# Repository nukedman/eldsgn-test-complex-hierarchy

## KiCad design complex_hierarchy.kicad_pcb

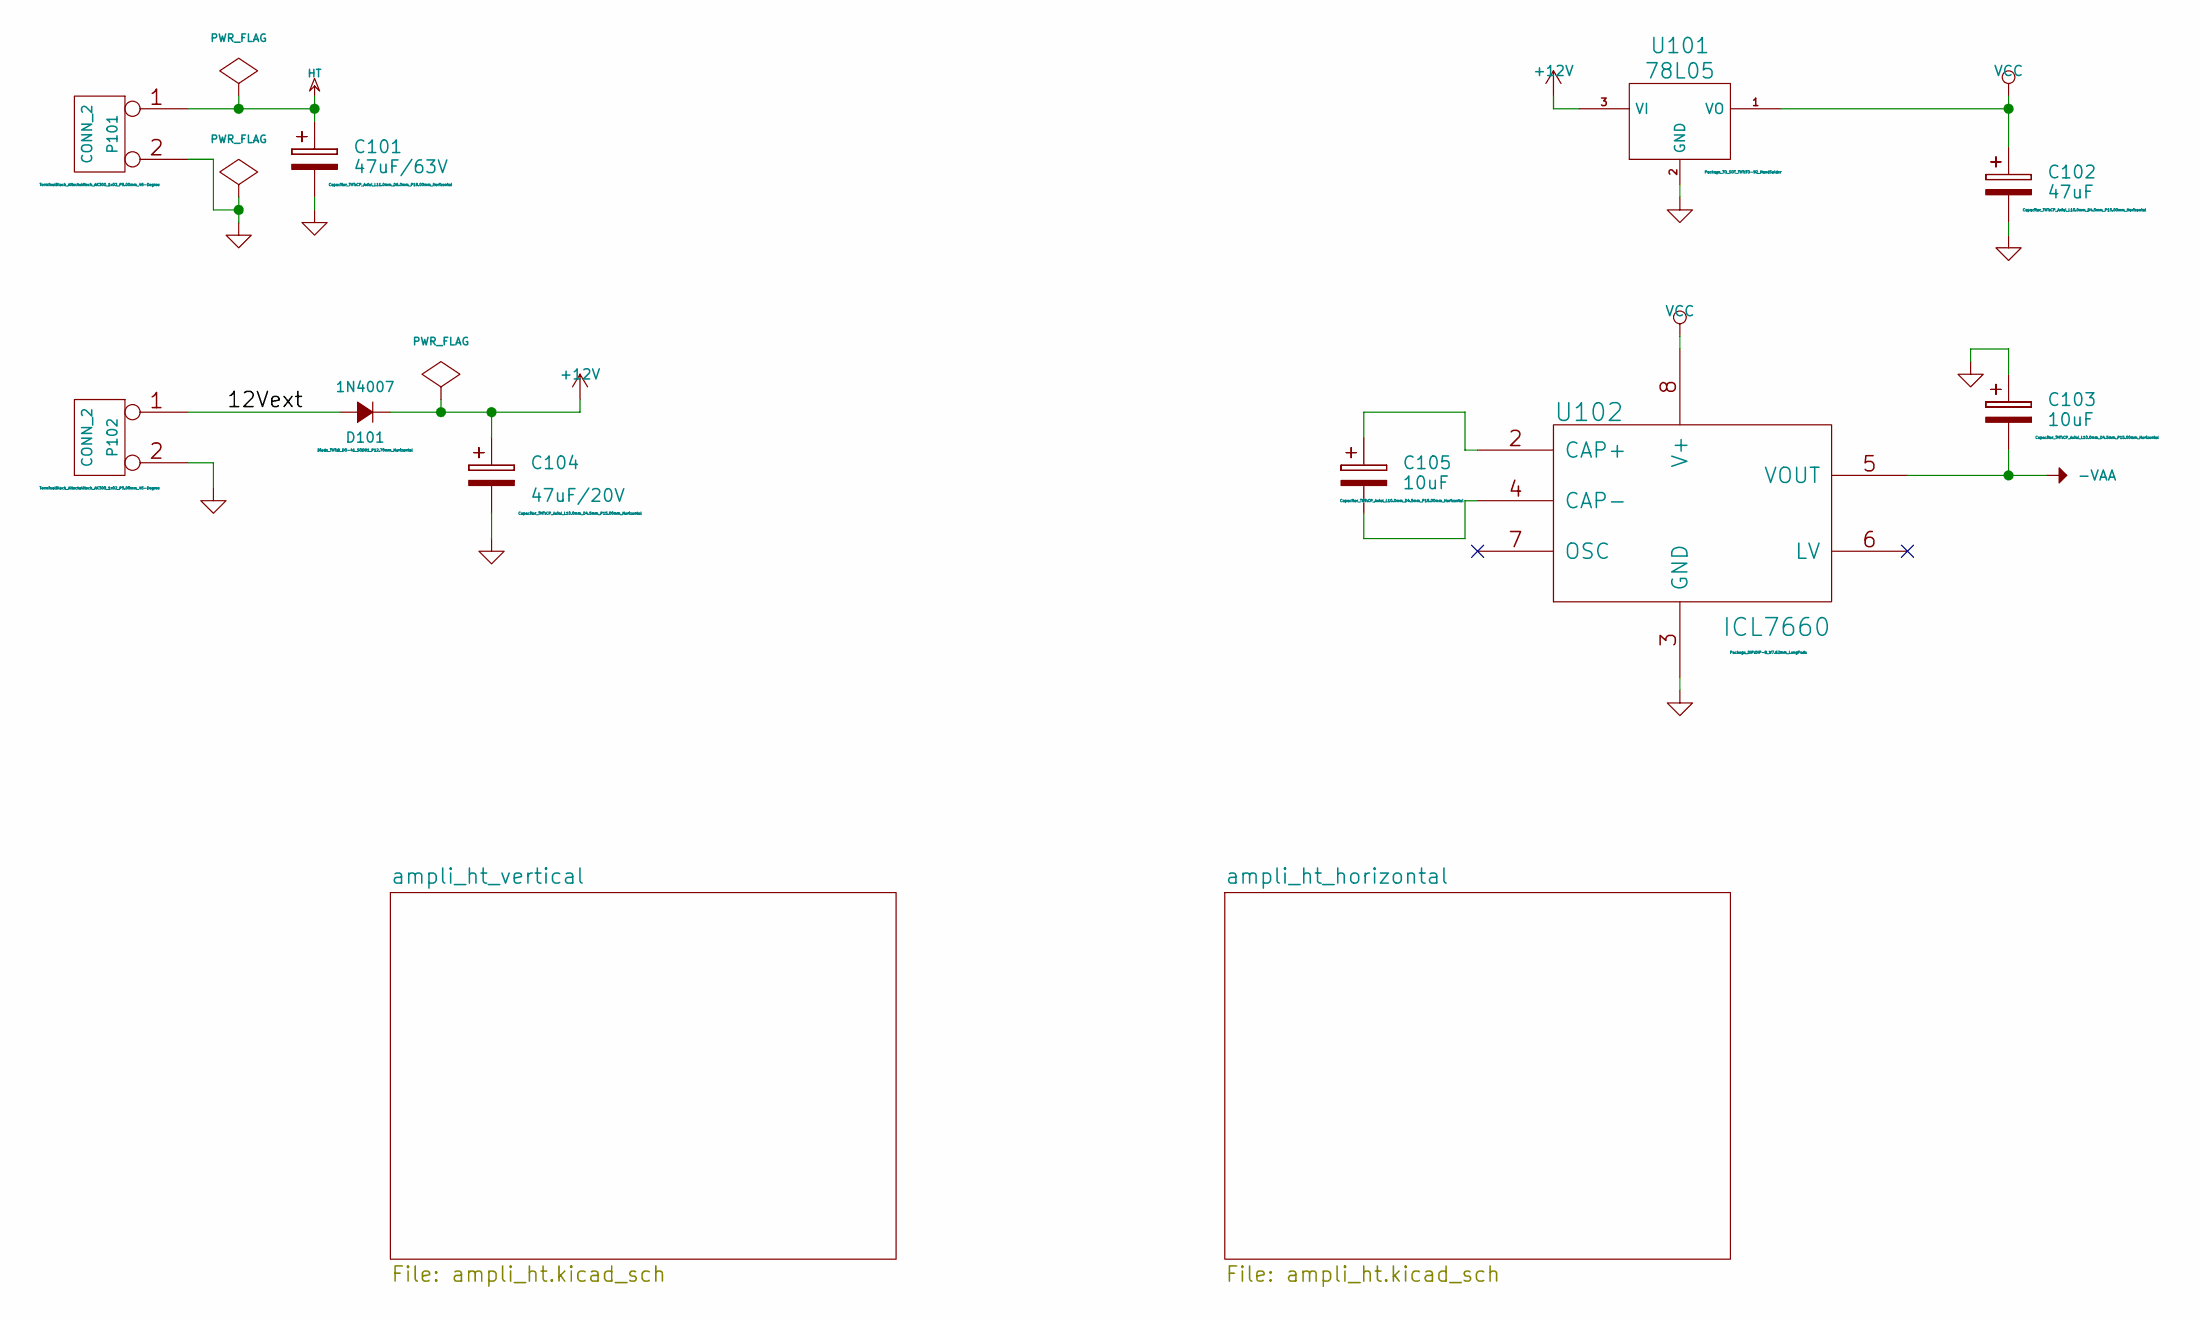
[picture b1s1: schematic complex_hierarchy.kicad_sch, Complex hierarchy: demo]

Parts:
C101: 47uF/63V; CP_Axial_L11.0mm_D6.0mm_P18.00mm_Horizontal
C102: 47uF; CP_Axial_L10.0mm_D4.5mm_P15.00mm_Horizontal
C103, C105: 10uF; CP_Axial_L10.0mm_D4.5mm_P15.00mm_Horizontal
C104: 47uF/20V; CP_Axial_L10.0mm_D4.5mm_P15.00mm_Horizontal
D101: 1N4007; D_DO-41_SOD81_P12.70mm_Horizontal
P101, P102: CONN_2; Altech_AK300_1x02_P5.00mm_45-Degree
U101: 78L05; TO-92_HandSolder
U102: ICL7660; DIP-8_W7.62mm_LongPads

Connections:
-VAA: C103.2, U102.5 (VOUT); also elsewhere on the board
/12Vext: D101.2 (A), P102.1
unnamed: C105.1, U102.2 (CAP+)
unnamed: C105.2, U102.4 (CAP-)
VCC: C102.1, U101.1 (VO), U102.8 (V+)

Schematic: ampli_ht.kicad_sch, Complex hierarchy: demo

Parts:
C201: 15nF; C_Disc_D5.0mm_W2.5mm_P5.00mm
C202: 150nF; C_Disc_D5.0mm_W2.5mm_P5.00mm
C203: 4.7nF; C_Disc_D5.0mm_W2.5mm_P5.00mm
C204: 820pF; C_Disc_D5.0mm_W2.5mm_P5.00mm
D201, D202, D203, D204: 1N4148; D_DO-35_SOD27_P7.62mm_Horizontal
P201, P202: CONN_2; Altech_AK300_1x02_P5.00mm_45-Degree
Q201, Q203: MPSA92; TO-92_HandSolder
Q202, Q204: MPSA42; TO-92_HandSolder
R1, R5: 0603WAF6201T5E; C4260; MPN 0603WAF6201T5E; LCSC Part C4260
R3: RC0402FR-07910RL2; C276279; MPN RC0402FR-07910RL; LCSC Part C276279
R201, R208, R212: 1K; R_Axial_DIN0204_L3.6mm_D1.6mm_P7.62mm_Horizontal
R202, R203: 22K; R_Axial_DIN0204_L3.6mm_D1.6mm_P7.62mm_Horizontal
R204: 470; R_Axial_DIN0204_L3.6mm_D1.6mm_P7.62mm_Horizontal
R205, R209, R210: 220K; R_Axial_DIN0204_L3.6mm_D1.6mm_P7.62mm_Horizontal
R206, R207: 47; R_Axial_DIN0204_L3.6mm_D1.6mm_P7.62mm_Horizontal
R211: 5,6K; R_Axial_DIN0204_L3.6mm_D1.6mm_P7.62mm_Horizontal
R213: 4,7K; R_Axial_DIN0204_L3.6mm_D1.6mm_P7.62mm_Horizontal
RV201: 4,7K; Potentiometer_Bourns_3266W_Vertical
U201: LM358N; DIP-8_W7.62mm_LongPads

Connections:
-VAA: U201.4 (V-); also elsewhere on the board
/ampli_ht_vertical/PIEZO_IN: P201.1, R1.1, R201.2
/ampli_ht_vertical/PIEZO_OUT: P202.1, R206.1, R207.1
/ampli_ht_vertical/S_OUT+: R209.1, R210.1, RV201.3
/ampli_ht_vertical/Vpil_0_3,3V: C201.1, R3.2, U201.3 (+), U201.6 (-), U201.7
unnamed: C201.2, R202.1, R203.2
unnamed: C202.1, R201.1, R202.2
unnamed: C204.1, R211.2
unnamed: D201.1 (K), D202.2 (A)
unnamed: D202.1 (K), Q201.2 (B), R205.1
unnamed: D203.2 (A), Q201.3 (C), Q202.2 (B)
unnamed: D203.1 (K), D204.2 (A)
unnamed: D204.1 (K), Q203.2 (B), Q204.3 (C), R211.1
unnamed: Q201.1 (E), R204.2
unnamed: Q202.1 (E), R206.2, R210.2
unnamed: Q203.1 (E), R207.2, R209.2
unnamed: Q204.2 (B), R208.1
unnamed: Q204.1 (E), R212.1
unnamed: R1.2, R3.1, R5.1 (1_1)
unnamed: R212.2, U201.1
unnamed: R213.1, RV201.1
unnamed: RV201.2, U201.2 (-)
unnamed: C203.1, R203.1, U201.5 (+)

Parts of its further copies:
C301: 15nF; C_Disc_D5.0mm_W2.5mm_P5.00mm
C302: 150nF; C_Disc_D5.0mm_W2.5mm_P5.00mm
C303: 4.7nF; C_Disc_D5.0mm_W2.5mm_P5.00mm
C304: 820pF; C_Disc_D5.0mm_W2.5mm_P5.00mm
D301, D302, D303, D304: 1N4148; D_DO-35_SOD27_P7.62mm_Horizontal
P301, P302: CONN_2; Altech_AK300_1x02_P5.00mm_45-Degree
Q301, Q303: MPSA92; TO-92_HandSolder
Q302, Q304: MPSA42; TO-92_HandSolder
R2, R6: 0603WAF6201T5E; C4260; MPN 0603WAF6201T5E; LCSC Part C4260
R4: RC0402FR-07910RL2; C276279; MPN RC0402FR-07910RL; LCSC Part C276279
R301, R308, R312: 1K; R_Axial_DIN0204_L3.6mm_D1.6mm_P7.62mm_Horizontal
R302, R303: 22K; R_Axial_DIN0204_L3.6mm_D1.6mm_P7.62mm_Horizontal
R304: 470; R_Axial_DIN0204_L3.6mm_D1.6mm_P7.62mm_Horizontal
R305, R309, R310: 220K; R_Axial_DIN0204_L3.6mm_D1.6mm_P7.62mm_Horizontal
R306, R307: 47; R_Axial_DIN0204_L3.6mm_D1.6mm_P7.62mm_Horizontal
R311: 5,6K; R_Axial_DIN0204_L3.6mm_D1.6mm_P7.62mm_Horizontal
R313: 4,7K; R_Axial_DIN0204_L3.6mm_D1.6mm_P7.62mm_Horizontal
RV301: 4,7K; Potentiometer_Bourns_3266W_Vertical
U301: LM358N; DIP-8_W7.62mm_LongPads

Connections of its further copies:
-VAA: U301.4 (V-); also elsewhere on the board
/ampli_ht_horizontal/PIEZO_IN: P301.1, R2.1, R301.2
/ampli_ht_horizontal/PIEZO_OUT: P302.1, R306.1, R307.1
/ampli_ht_horizontal/S_OUT+: R309.1, R310.1, RV301.3
/ampli_ht_horizontal/Vpil_0_3,3V: C301.1, R4.2, U301.3 (+), U301.6 (-), U301.7
unnamed: C301.2, R302.1, R303.2
unnamed: C302.1, R301.1, R302.2
unnamed: C304.1, R311.2
unnamed: D301.1 (K), D302.2 (A)
unnamed: D302.1 (K), Q301.2 (B), R305.1
unnamed: D303.2 (A), Q301.3 (C), Q302.2 (B)
unnamed: D303.1 (K), D304.2 (A)
unnamed: D304.1 (K), Q303.2 (B), Q304.3 (C), R311.1
unnamed: Q301.1 (E), R304.2
unnamed: Q302.1 (E), R306.2, R310.2
unnamed: Q303.1 (E), R307.2, R309.2
unnamed: Q304.2 (B), R308.1
unnamed: Q304.1 (E), R312.1
unnamed: R2.2, R4.1, R6.1 (1_1)
unnamed: R312.2, U301.1
unnamed: R313.1, RV301.1
unnamed: RV301.2, U301.2 (-)
unnamed: C303.1, R303.1, U301.5 (+)

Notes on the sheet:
Filter: Fc =1000Hz

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
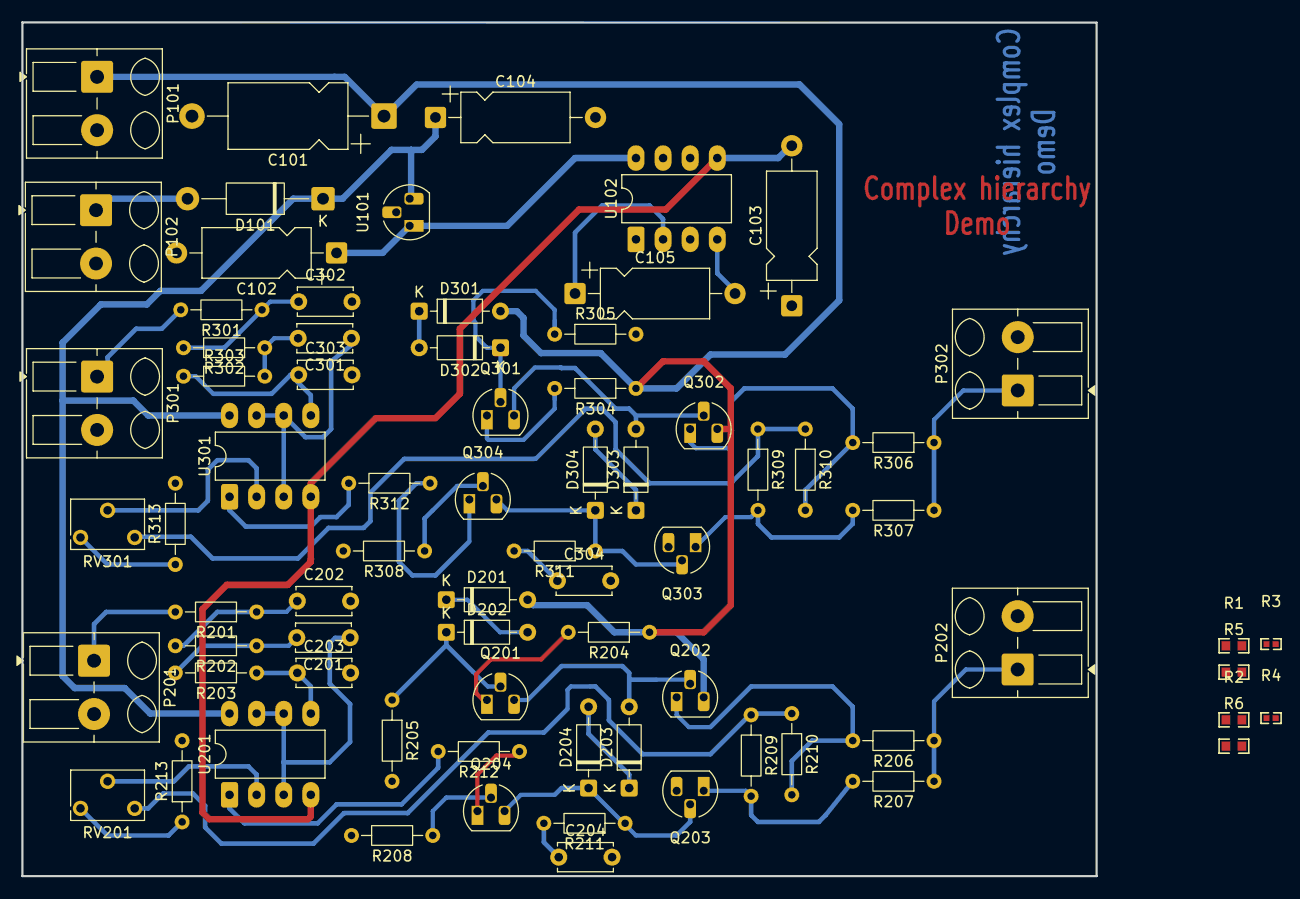
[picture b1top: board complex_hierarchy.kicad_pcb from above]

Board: 2 copper layers, 100.7 x 80.0 mm, 74 parts (0 on the bottom side), 52 nets.

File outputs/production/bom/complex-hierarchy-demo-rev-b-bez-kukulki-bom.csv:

"Reference","Value","Footprint","Quantity","DNP","ELDSGN_id","MPN","LCSC"
"C101","47uF/63V","Capacitor_THT:CP_Axial_L11.0mm_D6.0mm_P18.00mm_Horizontal","1","","","",""
"C102","47uF","Capacitor_THT:CP_Axial_L10.0mm_D4.5mm_P15.00mm_Horizontal","1","","","",""
"C103","10uF","Capacitor_THT:CP_Axial_L10.0mm_D4.5mm_P15.00mm_Horizontal","1","","","",""
"C104","47uF/20V","Capacitor_THT:CP_Axial_L10.0mm_D4.5mm_P15.00mm_Horizontal","1","","","",""
"C105","10uF","Capacitor_THT:CP_Axial_L10.0mm_D4.5mm_P15.00mm_Horizontal","1","","","",""
"C201","15nF","Capacitor_THT:C_Disc_D5.0mm_W2.5mm_P5.00mm","1","","","",""
"C202","150nF","Capacitor_THT:C_Disc_D5.0mm_W2.5mm_P5.00mm","1","","","",""
"C203","4.7nF","Capacitor_THT:C_Disc_D5.0mm_W2.5mm_P5.00mm","1","","","",""
"C204","820pF","Capacitor_THT:C_Disc_D5.0mm_W2.5mm_P5.00mm","1","","","",""
"C301","15nF","Capacitor_THT:C_Disc_D5.0mm_W2.5mm_P5.00mm","1","","","",""
"C302","150nF","Capacitor_THT:C_Disc_D5.0mm_W2.5mm_P5.00mm","1","","","",""
"C303","4.7nF","Capacitor_THT:C_Disc_D5.0mm_W2.5mm_P5.00mm","1","","","",""
"C304","820pF","Capacitor_THT:C_Disc_D5.0mm_W2.5mm_P5.00mm","1","","","",""
"D101","1N4007","Diode_THT:D_DO-41_SOD81_P12.70mm_Horizontal","1","","","",""
"D201","1N4148","Diode_THT:D_DO-35_SOD27_P7.62mm_Horizontal","1","","","",""
"D202","1N4148","Diode_THT:D_DO-35_SOD27_P7.62mm_Horizontal","1","","","",""
"D203","1N4148","Diode_THT:D_DO-35_SOD27_P7.62mm_Horizontal","1","","","",""
"D204","1N4148","Diode_THT:D_DO-35_SOD27_P7.62mm_Horizontal","1","","","",""
"D301","1N4148","Diode_THT:D_DO-35_SOD27_P7.62mm_Horizontal","1","","","",""
"D302","1N4148","Diode_THT:D_DO-35_SOD27_P7.62mm_Horizontal","1","","","",""
"D303","1N4148","Diode_THT:D_DO-35_SOD27_P7.62mm_Horizontal","1","","","",""
"D304","1N4148","Diode_THT:D_DO-35_SOD27_P7.62mm_Horizontal","1","","","",""
"P101","CONN_2","TerminalBlock_Altech:Altech_AK300_1x02_P5.00mm_45-Degree","1","","","",""
"P102","CONN_2","TerminalBlock_Altech:Altech_AK300_1x02_P5.00mm_45-Degree","1","","","",""
"P201","CONN_2","TerminalBlock_Altech:Altech_AK300_1x02_P5.00mm_45-Degree","1","","","",""
"P202","CONN_2","TerminalBlock_Altech:Altech_AK300_1x02_P5.00mm_45-Degree","1","","","",""
"P301","CONN_2","TerminalBlock_Altech:Altech_AK300_1x02_P5.00mm_45-Degree","1","","","",""
"P302","CONN_2","TerminalBlock_Altech:Altech_AK300_1x02_P5.00mm_45-Degree","1","","","",""
"Q201","MPSA92","Package_TO_SOT_THT:TO-92_HandSolder","1","","","",""
"Q202","MPSA42","Package_TO_SOT_THT:TO-92_HandSolder","1","","","",""
"Q203","MPSA92","Package_TO_SOT_THT:TO-92_HandSolder","1","","","",""
"Q204","MPSA42","Package_TO_SOT_THT:TO-92_HandSolder","1","","","",""
"Q301","MPSA92","Package_TO_SOT_THT:TO-92_HandSolder","1","","","",""
"Q302","MPSA42","Package_TO_SOT_THT:TO-92_HandSolder","1","","","",""
"Q303","MPSA92","Package_TO_SOT_THT:TO-92_HandSolder","1","","","",""
"Q304","MPSA42","Package_TO_SOT_THT:TO-92_HandSolder","1","","","",""
"R2","0603WAF6201T5E","connectors:C4260","1","","7","0603WAF6201T5E",""
"R3","RC0402FR-07910RL2","connectors:C276279","1","","11","RC0402FR-07910RL",""
"R4","RC0402FR-07910RL2","connectors:C276279","1","","7","RC0402FR-07910RL",""
"R5","0603WAF6201T5E","connectors:C4260","1","","7","0603WAF6201T5E",""
"R6","0603WAF6201T5E","connectors:C4260","1","","7","0603WAF6201T5E",""
"R201","1K","Resistor_THT:R_Axial_DIN0204_L3.6mm_D1.6mm_P7.62mm_Horizontal","1","","","",""
"R202","22K","Resistor_THT:R_Axial_DIN0204_L3.6mm_D1.6mm_P7.62mm_Horizontal","1","","","",""
"R203","22K","Resistor_THT:R_Axial_DIN0204_L3.6mm_D1.6mm_P7.62mm_Horizontal","1","","","",""
"R204","470","Resistor_THT:R_Axial_DIN0204_L3.6mm_D1.6mm_P7.62mm_Horizontal","1","","","",""
"R205","220K","Resistor_THT:R_Axial_DIN0204_L3.6mm_D1.6mm_P7.62mm_Horizontal","1","","","",""
"R206","47","Resistor_THT:R_Axial_DIN0204_L3.6mm_D1.6mm_P7.62mm_Horizontal","1","","","",""
"R207","47","Resistor_THT:R_Axial_DIN0204_L3.6mm_D1.6mm_P7.62mm_Horizontal","1","","","",""
"R208","1K","Resistor_THT:R_Axial_DIN0204_L3.6mm_D1.6mm_P7.62mm_Horizontal","1","","","",""
"R209","220K","Resistor_THT:R_Axial_DIN0204_L3.6mm_D1.6mm_P7.62mm_Horizontal","1","","","",""
"R210","220K","Resistor_THT:R_Axial_DIN0204_L3.6mm_D1.6mm_P7.62mm_Horizontal","1","","","",""
"R211","5,6K","Resistor_THT:R_Axial_DIN0204_L3.6mm_D1.6mm_P7.62mm_Horizontal","1","","","",""
"R212","1K","Resistor_THT:R_Axial_DIN0204_L3.6mm_D1.6mm_P7.62mm_Horizontal","1","","","",""
"R213","4,7K","Resistor_THT:R_Axial_DIN0204_L3.6mm_D1.6mm_P7.62mm_Horizontal","1","","","",""
"R301","1K","Resistor_THT:R_Axial_DIN0204_L3.6mm_D1.6mm_P7.62mm_Horizontal","1","","","",""
"R302","22K","Resistor_THT:R_Axial_DIN0204_L3.6mm_D1.6mm_P7.62mm_Horizontal","1","","","",""
"R303","22K","Resistor_THT:R_Axial_DIN0204_L3.6mm_D1.6mm_P7.62mm_Horizontal","1","","","",""
"R304","470","Resistor_THT:R_Axial_DIN0204_L3.6mm_D1.6mm_P7.62mm_Horizontal","1","","","",""
"R305","220K","Resistor_THT:R_Axial_DIN0204_L3.6mm_D1.6mm_P7.62mm_Horizontal","1","","","",""
"R306","47","Resistor_THT:R_Axial_DIN0204_L3.6mm_D1.6mm_P7.62mm_Horizontal","1","","","",""
"R307","47","Resistor_THT:R_Axial_DIN0204_L3.6mm_D1.6mm_P7.62mm_Horizontal","1","","","",""
"R308","1K","Resistor_THT:R_Axial_DIN0204_L3.6mm_D1.6mm_P7.62mm_Horizontal","1","","","",""
"R309","220K","Resistor_THT:R_Axial_DIN0204_L3.6mm_D1.6mm_P7.62mm_Horizontal","1","","","",""
"R310","220K","Resistor_THT:R_Axial_DIN0204_L3.6mm_D1.6mm_P7.62mm_Horizontal","1","","","",""
"R311","5,6K","Resistor_THT:R_Axial_DIN0204_L3.6mm_D1.6mm_P7.62mm_Horizontal","1","","","",""
"R312","1K","Resistor_THT:R_Axial_DIN0204_L3.6mm_D1.6mm_P7.62mm_Horizontal","1","","","",""
"R313","4,7K","Resistor_THT:R_Axial_DIN0204_L3.6mm_D1.6mm_P7.62mm_Horizontal","1","","","",""
"RV201","4,7K","Potentiometer_THT:Potentiometer_Bourns_3266W_Vertical","1","","","",""
"RV301","4,7K","Potentiometer_THT:Potentiometer_Bourns_3266W_Vertical","1","","","",""
"U101","78L05","Package_TO_SOT_THT:TO-92_HandSolder","1","","","",""
"U102","ICL7660","Package_DIP:DIP-8_W7.62mm_LongPads","1","","","",""
"U201","LM358N","Package_DIP:DIP-8_W7.62mm_LongPads","1","","","",""
"U301","LM358N","Package_DIP:DIP-8_W7.62mm_LongPads","1","","","",""
